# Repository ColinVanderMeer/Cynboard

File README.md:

# Cynboard
This is my submission for Hack Club Blueprint / sorta Hackpad V5. Thanks Cyaopad for serving as my go to board to look at when I had a problem.

## Features
- Hidden F13-F24 Keys for extra hotkeys in programs and games
- Midi layer for programs that don't accept anything but Midi

## PCB
| **Schematic** | **PCB** |
|---------------|---------|
|||

## CAD

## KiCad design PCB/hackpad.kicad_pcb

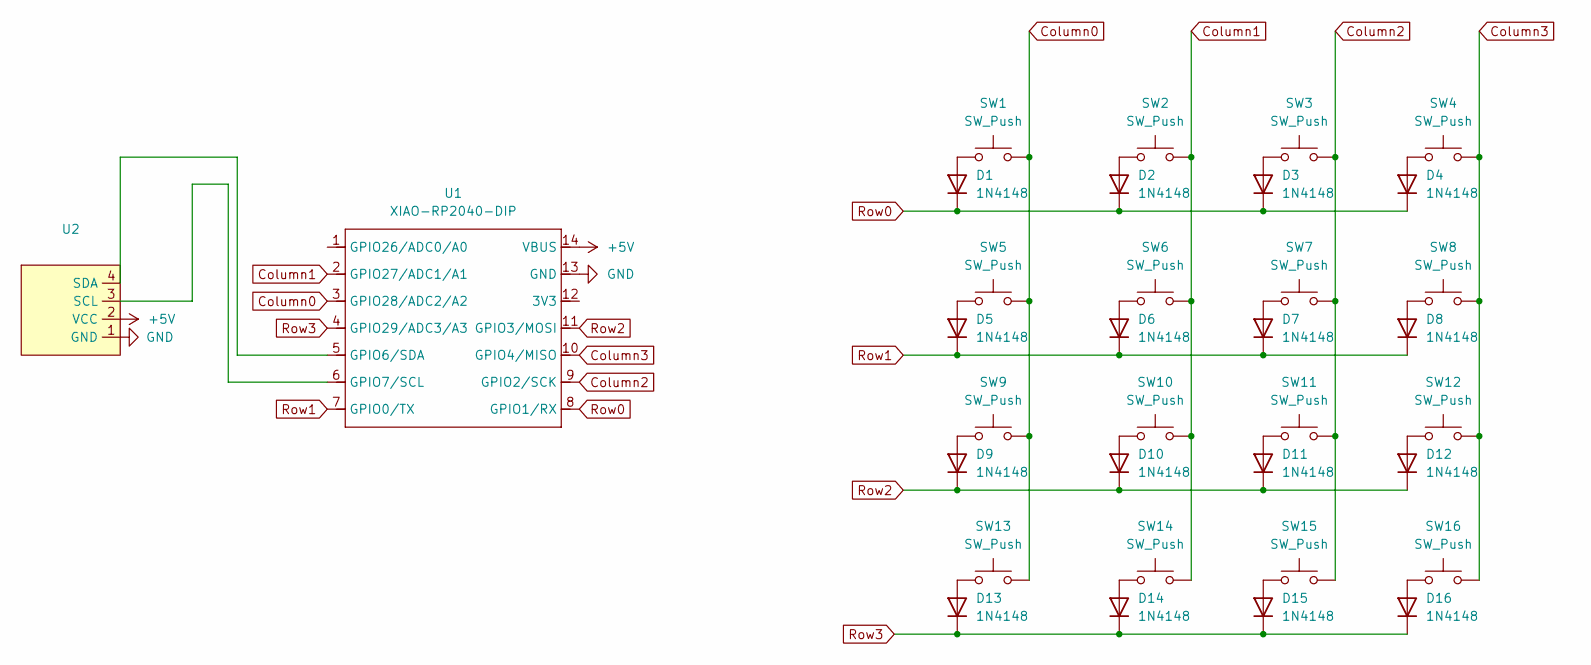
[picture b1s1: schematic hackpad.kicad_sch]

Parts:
D1, D2, D3, D4, D5, D6, D7, D8, D9, D10, D11, D12, D13, D14, D15, D16: 1N4148; D_DO-35_SOD27_P7.62mm_Horizontal
SW1, SW2, SW3, SW4, SW5, SW6, SW7, SW8, SW9, SW10, SW11, SW12, SW13, SW14, SW15, SW16: SW_Push; SW_Cherry_MX_1.00u_PCB
U1: XIAO-RP2040-DIP
U2: SSD1306-0.91-OLED-4pin-128x32

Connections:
+5V: U1.14 (VBUS), U2.2 (VCC)
Column0: SW1.2, SW5.2, SW9.2, SW13.2, U1.3 (GPIO28/ADC2/A2)
Column1: SW2.2, SW6.2, SW10.2, SW14.2, U1.2 (GPIO27/ADC1/A1)
Column2: SW3.2, SW7.2, SW11.2, SW15.2, U1.9 (GPIO2/SCK)
Column3: SW4.2, SW8.2, SW12.2, SW16.2, U1.10 (GPIO4/MISO)
GND: U1.13 (GND), U2.1 (GND)
unnamed: D1.2 (A), SW1.1
unnamed: D2.2 (A), SW2.1
unnamed: D3.2 (A), SW3.1
unnamed: D4.2 (A), SW4.1
unnamed: D5.2 (A), SW5.1
unnamed: D6.2 (A), SW6.1
unnamed: D7.2 (A), SW7.1
unnamed: D8.2 (A), SW8.1
unnamed: D9.2 (A), SW9.1
unnamed: D10.2 (A), SW10.1
unnamed: D11.2 (A), SW11.1
unnamed: D12.2 (A), SW12.1
unnamed: D13.2 (A), SW13.1
unnamed: D14.2 (A), SW14.1
unnamed: D15.2 (A), SW15.1
unnamed: D16.2 (A), SW16.1
unnamed: U1.5 (GPIO6/SDA), U2.4 (SDA)
unnamed: U1.6 (GPIO7/SCL), U2.3 (SCL)
Row0: D1.1 (K), D2.1 (K), D3.1 (K), D4.1 (K), U1.8 (GPIO1/RX)
Row1: D5.1 (K), D6.1 (K), D7.1 (K), D8.1 (K), U1.7 (GPIO0/TX)
Row2: D9.1 (K), D10.1 (K), D11.1 (K), D12.1 (K), U1.11 (GPIO3/MOSI)
Row3: D13.1 (K), D14.1 (K), D15.1 (K), D16.1 (K), U1.4 (GPIO29/ADC3/A3)

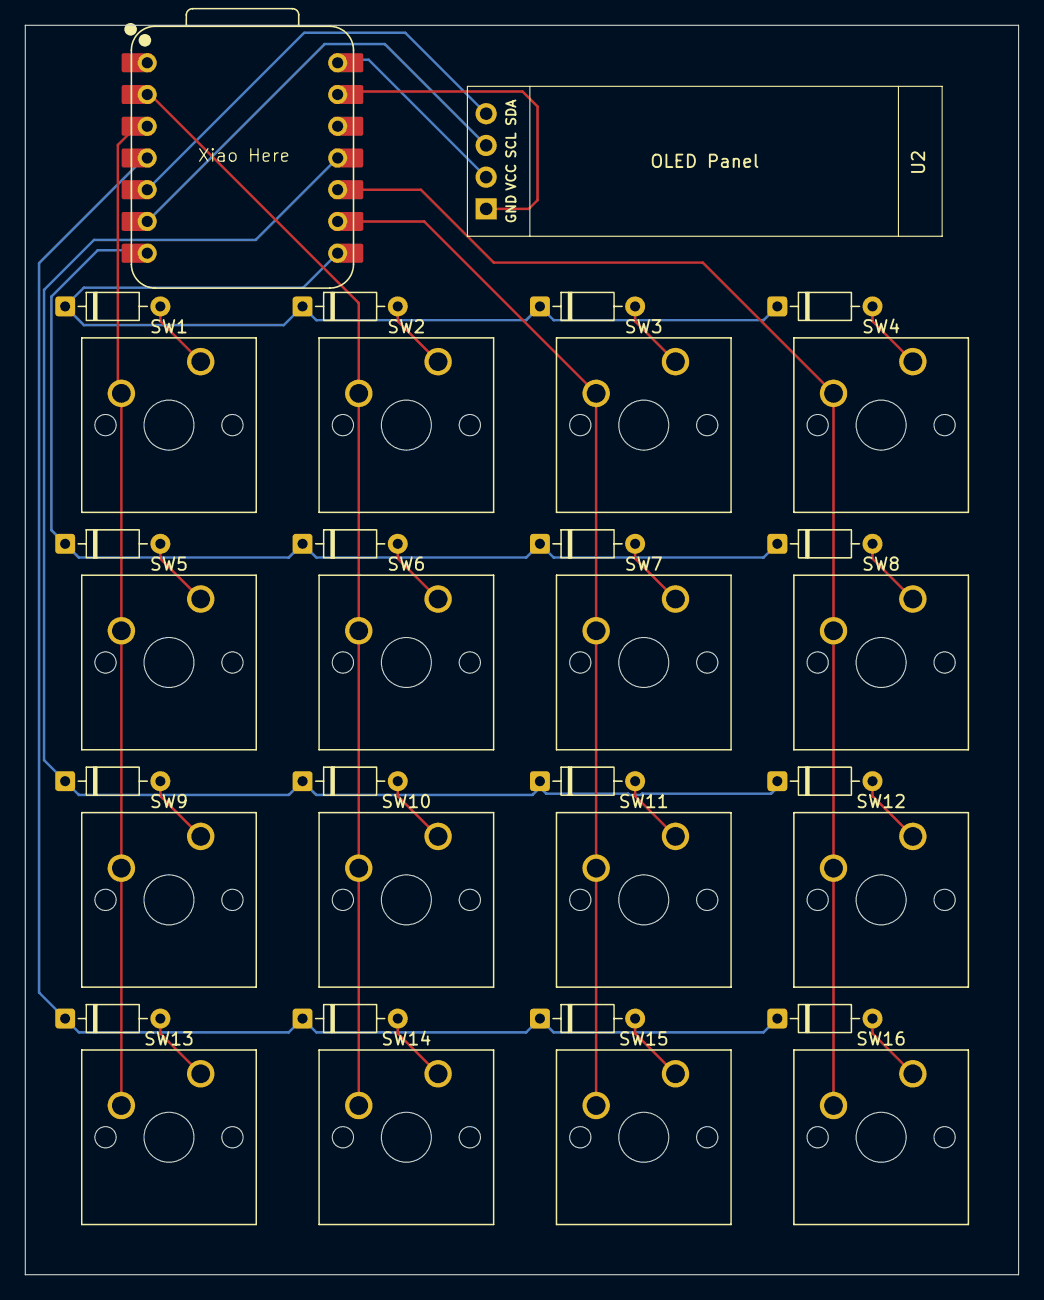
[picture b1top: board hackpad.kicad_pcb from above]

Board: 2 copper layers, 79.5 x 100.0 mm, 34 parts (0 on the bottom side), 28 nets.

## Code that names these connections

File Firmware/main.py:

# Cynboard firmware
import board
import busio

from kmk.kmk_keyboard import KMKKeyboard
from kmk.keys import KC
from kmk.scanners import DiodeOrientation
from kmk.modules.macros import Macros
# from kmk.extensions.display import Display, TextEntry, ImageEntry
# from kmk.extensions.display.ssd1306 import SSD1306
from kmk.modules.layers import Layers
from kmk.modules.midi import MidiKeys

COL0 = board.D2
COL1 = board.D1
COL2 = board.D7
COL3 = board.D8
ROW0 = board.D6
ROW1 = board.D5
ROW2 = board.D4
ROW3 = board.D3

# bus = busio.I2C(board.D9, board.D10)

# driver = SSD1306(i2c=bus, device_address=0x3C)

# display = Display(
#    display=driver,
#    width=128,
#    height=32,
#    dim_time=10,
#    dim_target=0.2,
#    off_time=1200,
#    brightness=0.8
# )

# display.entries = [
#        ImageEntry(image="cynboard.bmp", x=0, y=0),
#        # Couldn't find any conclusive way to change this text. Will have to test thing when I get the board
#        TextEntry(text='Layer 1', x=128, y=32, x_anchor="B", y_anchor="R"),
# ]

keyboard = KMKKeyboard()

macros = Macros()
keyboard.modules.append(macros)

# keyboard.extensions.append(display)

keyboard.modules.append(Layers())

keyboard.modules.append(MidiKeys())

keyboard.col_pins = (COL0, COL1, COL2, COL3)
keyboard.row_pins = (ROW0, ROW1, ROW2, ROW3)
keyboard.diode_orientation = DiodeOrientation.COL2ROW

FUNNY = KC.MACRO(":3")

keyboard.keymap = [
    #Normal Keymap
    [
        FUNNY, KC.MEH, KC.RELOAD, KC.TG(1),
        KC.F13, KC.F14, KC.F15, KC.F16,
        KC.F17, KC.F18, KC.F19, KC.F20,
        KC.F21, KC.F22, KC.F23, KC.F24
   ],
    # Midi Keymap
   [
       KC.MIDI_NOTE("F#4", 127), KC.MIDI_NOTE("G#4", 127), KC.MIDI_NOTE("A#4", 127), KC.TRNS,
       KC.MIDI_NOTE("F4", 127), KC.MIDI_NOTE("G4", 127), KC.MIDI_NOTE("A4", 127), KC.MIDI_NOTE("B4", 127),
       KC.MIDI_NOTE("C#4", 127), KC.MIDI_NOTE("D#4", 127), KC.NO, KC.NO,
       KC.MIDI_NOTE("C4", 127), KC.MIDI_NOTE("D4", 127), KC.MIDI_NOTE("E4", 127), KC.NO,
    ]
]

if __name__ == '__main__':
    keyboard.go()

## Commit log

2025-11-13 Upload for Blueprint
2026-01-01 Final update
2026-01-01 Fix PCB for if anyone tries to use this project for refrence
